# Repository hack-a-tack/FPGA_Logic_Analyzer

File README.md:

# FPGA Logic Analyzer

(NOTE TO SELF: THIS MUST BE UPDATED FOR THE FINAL REVISION; REV1 IS VIRTUALLY IRRELEVANT HERE, ONLY RELEVANT IN REPORT IF USED TO DISCUSS IMPORTANT DESIGN DECISIONS)

## Project overview

(Info applies to rev. 1, update for later revisions (only final rev. matters in the README))
FPGA-based 8-channel logic analyzer implemented on iCE40UP5K. Supports 24 MHz sampling, 4096 sample depth, UART streaming and trigger logic.

Key specs:
| Spec | Value |
| ------------- | ------------- |
| FPGA | iCE40UP5K |
| Sampling channels | 8 |
| Sampling rate | 24MHz |
| Buffer | 4096 samples |
| Interface | UART |
| Programming | SPI |
| PCB | 2-layer |
| Revision | 1. |

## Architecture

// Note to self: block diagram, + explain modules briefly (less than a full sentence for each)

(insert block diagram)

(module overview:)
| Module  | Description |
| ------------- | ------------- |
| capture_engine.vhd | samples digital inputs |
| analyzer_fsm.vhd | manages logic analyzer state |
| send_engine.vhd | UART streaming of captured data |
| ... | ... |

## Photos / board render

## Performance metrics
(table of performance metrics)
| Metric  | Value |
| ------------- | ------------- |
| Sample rate | 24MHz |
| Buffer depth | 4096 samples |
| UART throughput | 3Mbaud |
| Capture latency | 3 cycles |
| LUT usage | *1420* |
| BRAM usage | *4* |

## How to build / simulate
(Brief instructions)

## Lessons and improvements

## Link to engineering report
For a more in-depth overview, check out the project report (add github route and link).

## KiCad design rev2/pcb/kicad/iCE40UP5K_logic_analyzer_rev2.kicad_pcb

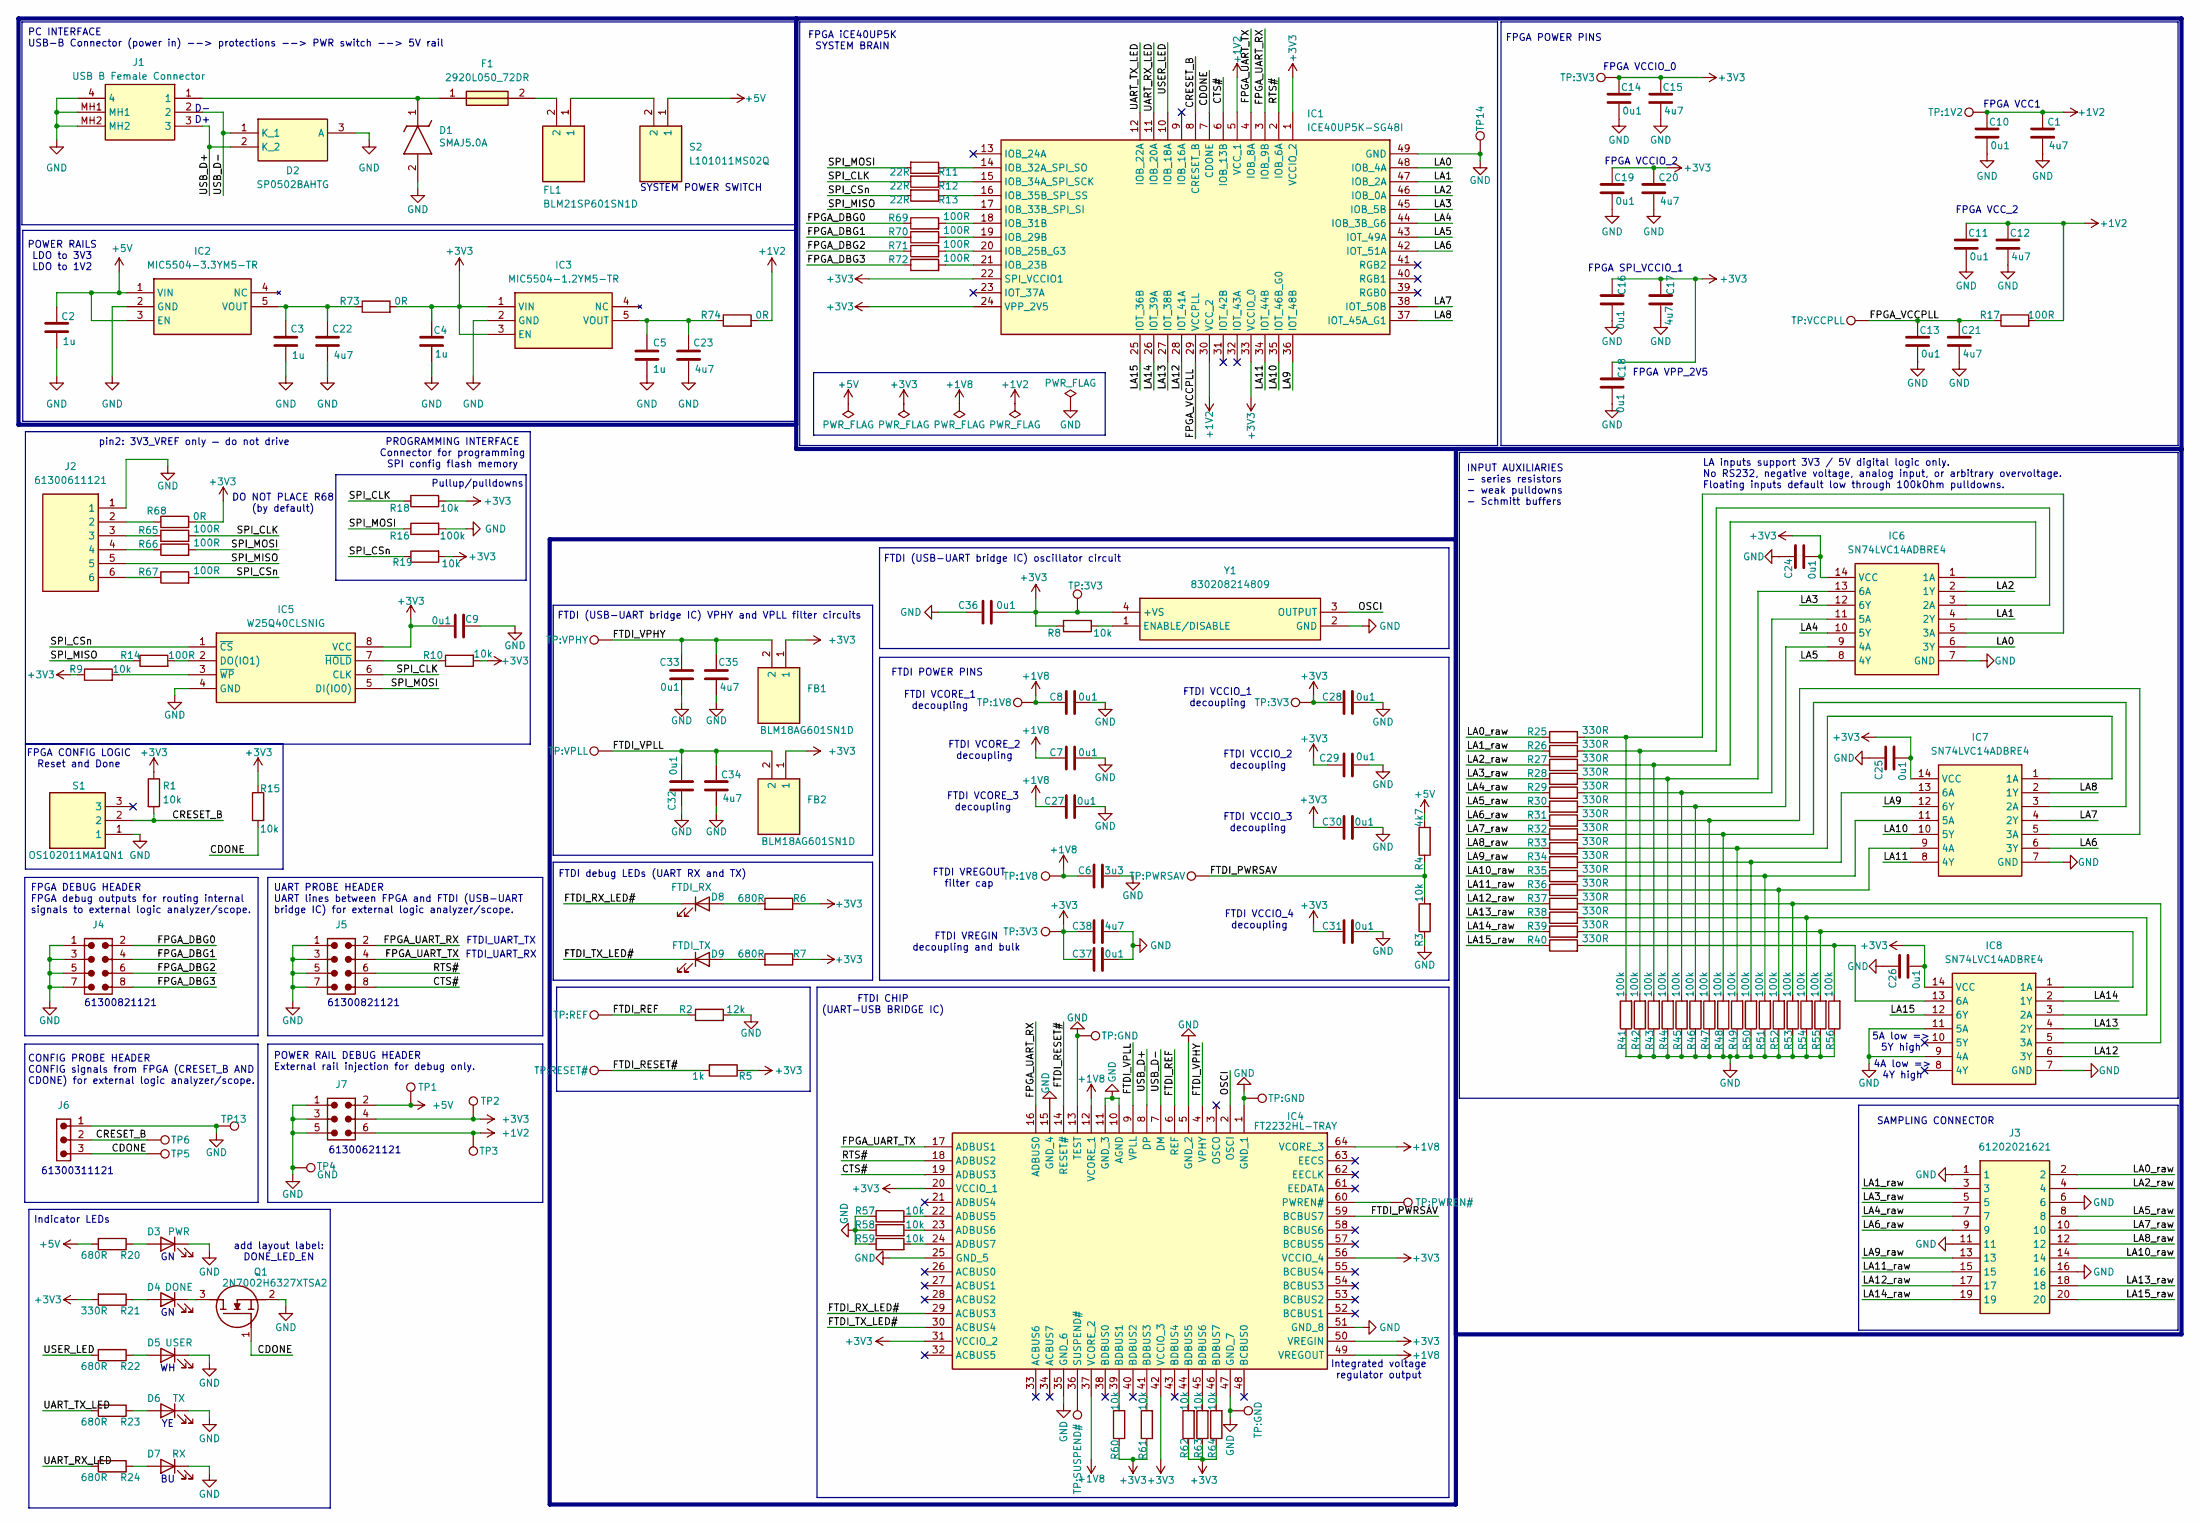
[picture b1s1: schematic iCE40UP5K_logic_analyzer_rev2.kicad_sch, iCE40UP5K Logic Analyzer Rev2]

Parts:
C1, C12, C15, C17, C20, C21, C22, C23, C34, C35, C38: 4u7; C0805
C2, C3, C4, C5: 1u; INDC1608X90N
C6: 3u3; C0805
C7, C8, C9, C10, C11, C13, C14, C16, C18, C19, C24, C25, C26, C27, C28, C29, C30, C31, C32, C33, C36, C37: 0u1; CAPC1608X95N
D1: SMAJ5.0A; DIOM5127X229N; Mouser Part Number 78-SMAJ5.0A
D2: SP0502BAHTG; SOT95P237X112-3N; Mouser Part Number 576-SP0502BAHTG
D3: PWR; 150060VS75003
D4: DONE; 150060VS75003
D5: USER; 150060WS75000
D6: TX; LEDC2012X70N
D7: RX; LEDC2012X85N
D8: FTDI_RX; LEDC2012X85N
D9: FTDI_TX; LEDC2012X70N
F1: 2920L050_72DR; FUSC7451X125N; Mouser Part Number 576-2920L050/72DR
FB1, FB2: BLM18AG601SN1D; BLM18SP221SN1B; Mouser Part Number 81-BLM11A601S
FL1: BLM21SP601SN1D; BLM21AG102BH1J; Mouser Part Number 81-BLM21SP601SN1D
IC1: ICE40UP5K-SG48I; QFN50P700X700X100-49N-D; Mouser Part Number 842-ICE40UP5K-SG48I
IC2: MIC5504-3.3YM5-TR; SOT95P280X145-5N; Mouser Part Number 998-MIC5504-3.3YM5TR
IC3: MIC5504-1.2YM5-TR; SOT95P280X145-5N; Mouser Part Number 998-MIC5504-1.2YM5TR
IC4: FT2232HL-TRAY; QFP50P1200X1200X160-64N; Mouser Part Number 895-FT2232HL-TRAY
IC5: W25Q40CLSNIG; SOIC127P600X175-8N; Mouser Part Number 454-W25Q40CLSNIG
IC6, IC7, IC8: SN74LVC14ADBRE4; SOP65P780X200-14N; Mouser Part Number 595-SN74LVC14ADBRE4
J1: USB B Female Connector; 61400416121; Mouser Part Number 710-61400416121
J2: 61300611121; HDRV6W64P0X254_1X6_1524X254X869P; Mouser Part Number 710-61300611121
J3: 61202021621; SHDR20W64P254_2X10_3306X910X885P; Mouser Part Number 710-61202021621
J4, J5: 61300821121; J_Wurth_WR-PHD_61300821121
J6: 61300311121; J_Wurth_WR-PHD_61300311121
J7: 61300621121; J_Wurth_WR-PHD_61300621121
Q1: 2N7002H6327XTSA2; SOT95P240X110-3N; Mouser Part Number 726-2N7002H6327XTSA2
R1, R3, R8, R9, R10, R15, R18, R19, R57, R58, R59, R60, R61, R62, R63, R64: 10k; R_0603_1608Metric
R2: 12k; R_0603_1608Metric
R4: 4k7; R_0603_1608Metric
R5: 1k; R_0603_1608Metric
R6, R7, R20, R22, R23, R24: 680R; R_0603_1608Metric
R11, R12, R13: 22R; R_0603_1608Metric
R14, R17, R65, R66, R67, R69, R70, R71, R72: 100R; R_0603_1608Metric
R16, R41, R42, R43, R44, R45, R46, R47, R48, R49, R50, R51, R52, R53, R54, R55, R56: 100k; R_0603_1608Metric
R21, R25, R26, R27, R28, R29, R30, R31, R32, R33, R34, R35, R36, R37, R38, R39, R40: 330R; R_0603_1608Metric
R68, R73, R74: 0R; R_0805_2012Metric
S1: OS102011MA1QN1; Mouser Part Number 611-OS102011MA1QN1
S2: L101011MS02Q; Mouser Part Number 611-L101011MS02Q
TP1: 5V; TestPoint_Pad_D1.5mm
TP2: 3V3; TestPoint_Pad_D1.5mm
TP3: 1V2; TestPoint_Pad_D1.5mm
TP4: GND; TestPoint_Pad_D1.5mm
TP5: CDONE; TestPoint_Pad_D1.0mm
TP6: CRESET_B; TestPoint_Pad_D1.0mm
TP13, TP14: GND; TestPoint_Pad_D1.0mm
TP:1V2: VCC; TestPoint_Pad_D1.0mm
TP:1V8: VREGOUT; TestPoint_Pad_D1.0mm
TP:3V3: FTDI_VCCIO; TestPoint_Pad_D1.0mm
TP:GND: GND; TestPoint_Pad_D1.0mm
TP:PWREN#: PWREN#; TestPoint_Pad_D1.0mm
TP:PWRSAV: PWRSAV#; TestPoint_Pad_D1.0mm
TP:REF: REF; TestPoint_Pad_D1.0mm
TP:RESET#: RESET#; TestPoint_Pad_D1.0mm
TP:SUSPEND#: SUSPEND#; TestPoint_Pad_D1.0mm
TP:VCCPLL: VCC_PLL; TestPoint_Pad_D1.0mm
TP:VPHY: VPHY; TestPoint_Pad_D1.0mm
TP:VPLL: VPLL; TestPoint_Pad_D1.0mm
Y1: 830208214809; Manufacturer_Part_Number 830208214809

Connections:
+1V2: C1.1, C10.1, C11.1, C12.1, IC1.5 (VCC_1), IC1.30 (VCC_2), J7.6, R17.2, R74.2, TP3.1, TP:1V2.1
+1V8: C6.1, C7.1, C8.1, C27.1, IC4.12 (VCORE_1), IC4.37 (VCORE_2), IC4.49 (VREGOUT), IC4.64 (VCORE_3), TP:1V8.1; also elsewhere on the board
+3V3: C4.1, C9.2, C14.1, C15.1, C16.1, C17.1, C18.1, C19.1, C20.1, C24.2, C25.2, C26.2, C28.1, C29.1, C30.1, C31.1, C36.2, C37.1, C38.1, FB1.1, FB2.1, IC1.1 (VCCIO_2), IC1.22 (SPI_VCCIO1), IC1.24 (VPP_2V5), IC1.33 (VCCIO_0), IC3.1 (VIN), IC3.3 (EN), IC4.20 (VCCIO_1), IC4.31 (VCCIO_2), IC4.42 (VCCIO_3), IC4.50 (VREGIN), IC4.56 (VCCIO_4), IC5.8 (VCC), IC6.14 (VCC), IC7.14 (VCC), IC8.14 (VCC), J7.4, R1.1, R5.1, R6.1, R7.1, R8.2, R9.1, R10.2, R15.1, R18.2, R19.2, R21.2, R60.1, R61.1, R62.1, R63.1, R64.1, R68.2, R73.2, TP2.1, TP:3V3.1, Y1.4 (+VS); also elsewhere on the board
+5V: C2.1, IC2.1 (VIN), IC2.3 (EN), J7.2, R4.2, R20.2, S2.1, TP1.1
/CDONE: IC1.7 (CDONE), J6.3, Q1.1 (G), R15.2, TP5.1
/CRESET_B: IC1.8 (CRESET_B), J6.2, R1.2, S1.2, TP6.1
/CTS#: IC1.6 (IOB_13B), IC4.19 (ADBUS3), J5.8
/FPGA_DBG0: J4.2, R69.1
/FPGA_DBG1: J4.4, R70.1
/FPGA_DBG2: J4.6, R71.1
/FPGA_DBG3: J4.8, R72.1
/FPGA_UART_RX: IC1.3 (IOB_9B), IC4.16 (ADBUS0), J5.2
/FPGA_UART_TX: IC1.4 (IOB_8A), IC4.17 (ADBUS1), J5.4
/FPGA_VCCPLL: C13.1, C21.1, IC1.29 (VCCPLL), R17.1, TP:VCCPLL.1
/FTDI_PWRSAV: IC4.59 (BCBUS7), R3.2, R4.1, TP:PWRSAV.1
/FTDI_REF: IC4.6 (REF), R2.1, TP:REF.1
/FTDI_RESET#: IC4.14 (RESET#), R5.2, TP:RESET#.1
/FTDI_RX_LED#: D8.1 (K), IC4.29 (ACBUS3)
/FTDI_TX_LED#: D9.1 (K), IC4.30 (ACBUS4)
/FTDI_VPHY: C33.2, C35.1, FB1.2, IC4.4 (VPHY), TP:VPHY.1
/FTDI_VPLL: C32.2, C34.1, FB2.2, IC4.9 (VPLL), TP:VPLL.1
/LA0: IC1.48 (IOB_4A), IC6.6 (3Y)
/LA0_raw: J3.2, R25.1
/LA1: IC1.47 (IOB_2A), IC6.4 (2Y)
/LA1_raw: J3.3, R26.1
/LA2: IC1.46 (IOB_0A), IC6.2 (1Y)
/LA2_raw: J3.4, R27.1
/LA3: IC1.45 (IOB_5B), IC6.12 (6Y)
/LA3_raw: J3.5, R28.1
/LA4: IC1.44 (IOB_3B_G6), IC6.10 (5Y)
/LA4_raw: J3.7, R29.1
/LA5: IC1.43 (IOT_49A), IC6.8 (4Y)
/LA5_raw: J3.8, R30.1
/LA6: IC1.42 (IOT_51A), IC7.6 (3Y)
/LA6_raw: J3.9, R31.1
/LA7: IC1.38 (IOT_50B), IC7.4 (2Y)
/LA7_raw: J3.10, R32.1
/LA8: IC1.37 (IOT_45A_G1), IC7.2 (1Y)
/LA8_raw: J3.12, R33.1
/LA9: IC1.36 (IOT_48B), IC7.12 (6Y)
/LA9_raw: J3.13, R34.1
/LA10: IC1.35 (IOT_46B_G0), IC7.10 (5Y)
/LA10_raw: J3.14, R35.1
/LA11: IC1.34 (IOT_44B), IC7.8 (4Y)
/LA11_raw: J3.15, R36.1
/LA12: IC1.28 (IOT_41A), IC8.6 (3Y)
/LA12_raw: J3.17, R37.1
/LA13: IC1.27 (IOT_38B), IC8.4 (2Y)
/LA13_raw: J3.18, R38.1
/LA14: IC1.26 (IOT_39A), IC8.2 (1Y)
/LA14_raw: J3.19, R39.1
/LA15: IC1.25 (IOT_36B), IC8.12 (6Y)
/LA15_raw: J3.20, R40.1
/OSCI: IC4.2 (OSCI), Y1.3 (OUTPUT)
/RTS#: IC1.2 (IOB_6A), IC4.18 (ADBUS2), J5.6
/SPI_CLK: IC5.6 (CLK), R12.2, R18.1, R65.2
/SPI_CSn: IC5.1 (~CS), R13.2, R19.1, R67.2
/SPI_MISO: IC1.17 (IOB_33B_SPI_SI), J2.5, R14.1
/SPI_MOSI: IC5.5 (DI(IO0)), R11.2, R16.1, R66.2
/UART_RX_LED: IC1.11 (IOB_20A), R24.2
/UART_TX_LED: IC1.12 (IOB_22A), R23.2
/USB_D+: D2.2 (K_2), IC4.8 (DP), J1.3
/USB_D-: D2.1 (K_1), IC4.7 (DM), J1.2
/USER_LED: IC1.10 (IOB_18A), R22.2
GND: C1.2, C2.2, C3.2, C4.2, C5.2, C6.2, C7.2, C8.2, C9.1, C10.2, C11.2, C12.2, C13.2, C14.2, C15.2, C16.2, C17.2, C18.2, C19.2, C20.2, C21.2, C22.2, C23.2, C24.1, C25.1, C26.1, C27.2, C28.2, C29.2, C30.2, C31.2, C32.1, C33.1, C34.2, C35.2, C36.1, C37.2, C38.2, D1.2 (A), D2.3 (A), D3.1 (K), D5.1 (K), D6.1 (K), D7.1 (K), IC1.49 (GND), IC2.2 (GND), IC3.2 (GND), IC4.1 (GND_1), IC4.5 (GND_2), IC4.10 (AGND), IC4.11 (GND_3), IC4.13 (TEST), IC4.15 (GND_4), IC4.25 (GND_5), IC4.35 (GND_6), IC4.47 (GND_7), IC4.51 (GND_8), IC5.4 (GND), IC6.7 (GND), IC7.7 (GND), IC8.7 (GND), IC8.9 (4A), IC8.11 (5A), J1.4, J1.MH1, J1.MH2, J2.1, J3.1, J3.6, J3.11, J3.16, J4.1, J4.3, J4.5, J4.7, J5.1, J5.3, J5.5, J5.7, J6.1, J7.1, J7.3, J7.5, Q1.2 (S), R2.2, R3.1, R16.2, R41.1, R42.1, R43.1, R44.1, R45.1, R46.1, R47.1, R48.1, R49.1, R50.1, R51.1, R52.1, R53.1, R54.1, R55.1, R56.1, R57.1, R58.1, R59.1, S1.1, TP4.1, TP13.1, TP14.1, TP:GND.1, Y1.2 (GND); also elsewhere on the board
unnamed: D1.1 (K), F1.1, J1.1
unnamed: D3.2 (A), R20.1
unnamed: D4.2 (A), R21.1
unnamed: D4.1 (K), Q1.3 (D)
unnamed: D5.2 (A), R22.1
unnamed: D6.2 (A), R23.1
unnamed: D7.2 (A), R24.1
unnamed: D8.2 (A), R6.2
unnamed: D9.2 (A), R7.2
unnamed: F1.2, FL1.2
unnamed: FL1.1, S2.2
unnamed: IC1.21 (IOB_23B), R72.2
unnamed: IC1.20 (IOB_25B_G3), R71.2
unnamed: IC1.19 (IOB_29B), R70.2
unnamed: IC1.18 (IOB_31B), R69.2
unnamed: IC1.14 (IOB_32A_SPI_SO), R11.1
unnamed: IC1.15 (IOB_34A_SPI_SCK), R12.1
unnamed: IC1.16 (IOB_35B_SPI_SS), R13.1
unnamed: C3.1, C22.1, IC2.5 (VOUT), R73.1
unnamed: C5.1, C23.1, IC3.5 (VOUT), R74.1
unnamed: IC4.22 (ADBUS5), R57.2
unnamed: IC4.23 (ADBUS6), R58.2
unnamed: IC4.24 (ADBUS7), R59.2
unnamed: IC4.39 (BDBUS1), R60.2
unnamed: IC4.41 (BDBUS3), R61.2
unnamed: IC4.44 (BDBUS5), R62.2
unnamed: IC4.45 (BDBUS6), R63.2
unnamed: IC4.46 (BDBUS7), R64.2
unnamed: IC4.60 (PWREN#), TP:PWREN#.1
unnamed: IC4.36 (SUSPEND#), TP:SUSPEND#.1
unnamed: IC5.2 (DO(IO1)), R14.2
unnamed: IC5.7 (~HOLD), R10.1
unnamed: IC5.3 (~WP), R9.2
unnamed: IC6.1 (1A), R27.2, R43.2
unnamed: IC6.3 (2A), R26.2, R42.2
unnamed: IC6.5 (3A), R25.2, R41.2
unnamed: IC6.9 (4A), R30.2, R46.2
unnamed: IC6.11 (5A), R29.2, R45.2
unnamed: IC6.13 (6A), R28.2, R44.2
unnamed: IC7.1 (1A), R33.2, R49.2
unnamed: IC7.3 (2A), R32.2, R48.2
unnamed: IC7.5 (3A), R31.2, R47.2
unnamed: IC7.9 (4A), R36.2, R52.2
unnamed: IC7.11 (5A), R35.2, R51.2
unnamed: IC7.13 (6A), R34.2, R50.2
unnamed: IC8.1 (1A), R39.2, R55.2
unnamed: IC8.3 (2A), R38.2, R54.2
unnamed: IC8.5 (3A), R37.2, R53.2
unnamed: IC8.13 (6A), R40.2, R56.2
unnamed: J2.2, R68.1
unnamed: J2.3, R65.1
unnamed: J2.4, R66.1
unnamed: J2.6, R67.1
unnamed: R8.1, Y1.1 (ENABLE/DISABLE)

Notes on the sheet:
FPGA VCCIO_2
FPGA VCC1
POWER RAILS LDO to 3V3 LDO to 1V2
FTDI VCORE_3 decoupling
FTDI VCCIO_1 decoupling
61300311121
5A low => 5Y high
FTDI VCCIO_2 decoupling
PROGRAMMING INTERFACE Connector for programming SPI config flash memory
FTDI_UART_RX
FTDI VCORE_1 decoupling
SAMPLING CONNECTOR
CONFIG PROBE HEADER CONFIG signals from FPGA (CRESET_B AND CDONE) for external logic analyzer/scope.
LA inputs support 3V3 / 5V digital logic only. No RS232, negative voltage, analog input, or arbitrary overvoltage. Floating inputs default low through 100kOhm pulldowns.
61300821121
add layout label: DONE_LED_EN
FPGA CONFIG LOGIC Reset and Done
UART PROBE HEADER UART lines between FPGA and FTDI (USB-UART bridge IC) for external logic analyzer/scope.
61300621121
POWER RAIL DEBUG HEADER External rail injection for debug only.
D- D+
FPGA SPI_VCCIO_1
FTDI VREGIN decoupling and bulk
FPGA POWER PINS
FTDI VCCIO_4 decoupling
FPGA DEBUG HEADER FPGA debug outputs for routing internal signals to external logic analyzer/scope.
FTDI VREGOUT filter cap
FPGA VCC_2
FTDI (USB-UART bridge IC) VPHY and VPLL filter circuits
Indicator LEDs
FTDI CHIP (UART-USB BRIDGE IC)
FTDI VCCIO_3 decoupling
FTDI (USB-UART bridge IC) oscillator circuit
FTDI debug LEDs (UART RX and TX)
Pullup/pulldowns
FPGA iCE40UP5K SYSTEM BRAIN
Integrated voltage regulator output
FTDI POWER PINS
FPGA VPP_2V5
pin2: 3V3_VREF only — do not drive

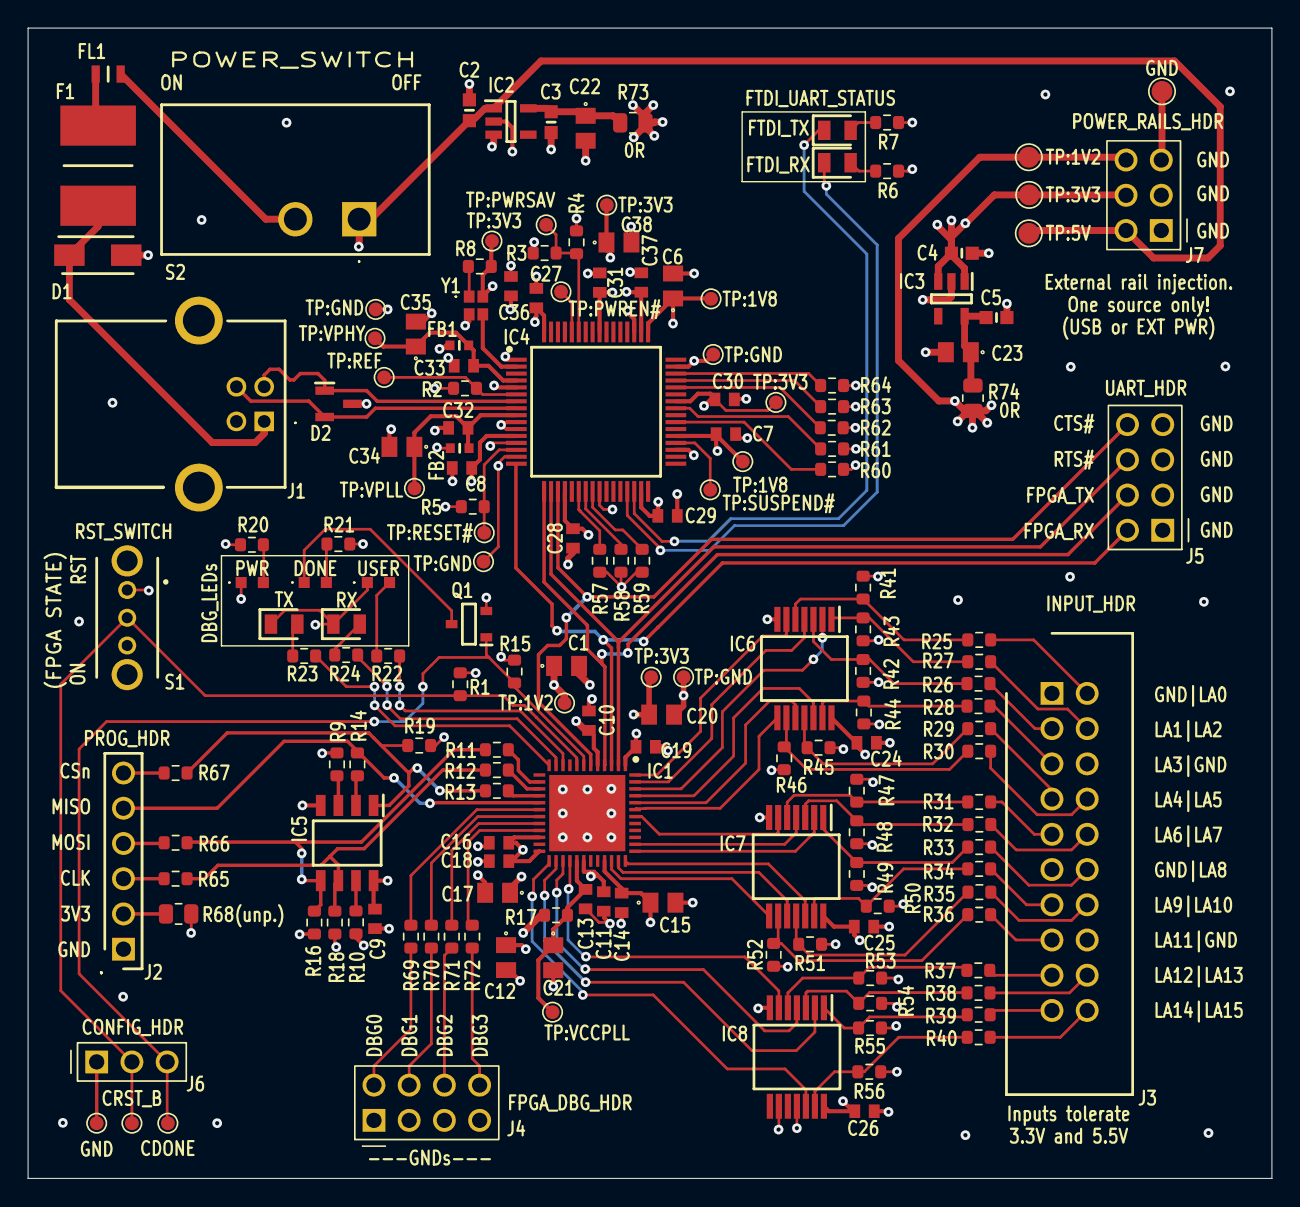
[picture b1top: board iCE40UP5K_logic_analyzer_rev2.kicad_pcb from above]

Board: 4 copper layers, 89.7 x 82.9 mm, 170 parts (0 on the bottom side), 119 nets.

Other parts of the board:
TP:1V8#2: VREGOUT; TestPoint_Pad_D1.0mm
TP:3V3#2: FTDI_VCCIO; TestPoint_Pad_D1.0mm
TP:3V3#3: VCCIO; TestPoint_Pad_D1.0mm
TP:3V3#4: VS_OSC; TestPoint_Pad_D1.0mm
TP:GND#2: GND; TestPoint_Pad_D1.0mm
TP:GND#3: TEST; TestPoint_Pad_D1.0mm

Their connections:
+1V8: TP:1V8#2.1; also elsewhere on the board
+3V3: TP:3V3#2.1, TP:3V3#3.1, TP:3V3#4.1; also elsewhere on the board
GND: TP:GND#2.1, TP:GND#3.1; also elsewhere on the board

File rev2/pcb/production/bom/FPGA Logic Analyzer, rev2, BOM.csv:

Id,Reference Designator,MPN,Qty,Description,Notes
1,IC1,ICE40UP5K-SG48I,1,"FPGA, iCE40 UP5K",
2,IC2,MIC5504-3.3YM5-TR,1,LDO (5 V to 3.3 V),
3,IC3,MIC5504-1.2YM5-TR,1,LDO (3.3 V to 1.2 V),
4,IC4,FT2232HL-REEL,1,USB-UART bridge IC,Out of stock. Buy from LCSC instead. FT2232HL-REEL
5,IC5,W25Q40CLSNIG,1,"Memory, SPI config flash, 16 Mbit","Out of stock. But can ignore since have left over from rev1. If not, replace with similar other SOIC-8"
6,"IC6, IC7, IC8",SN74LVC14ADBRE4,3,"Schmitt trigger buffer, 8 channel",
7,F1,2920L050/72DR,1,500 mA PTC polyfuse,
8,FL1,BLM21SP601SN1D,1,"2.3 A, 600 Ω ferrite bead",
9,"FB1, FB2",BLM18AG601SN1D,2,"600 Ω @ high frequency / 100 MHz class, 500 mA max DC current, 0.38 Ω max DCR, 0603",
10,Q1,2N7002H6327XTSA2,1,"NMOS, N-Ch 60V 300mA SOT-23-3, (LED driver)",
11,Y1,830208214809,1,Clock for bridge IC (Standard Clock Oscillators WE-SPXO 12.0MHz 25ppm 2.0 x 1.6mm),
12,D1,SMAJ5.0A,1,5 V unidirectional TVS diode / ESD protection,
13,D2,SP0502BAHTG,1,Data-line TVS diodes,
14,"D3, D4",150060VS75003,2,"0805 SMD LED, GN",
15,D5,150060WS75000,1,"0805 SMD LED, WH","Out of stock. But can ignore since we have one left over from rev1 (otherwise, sub with other coloured LED)"
16,"D6, D9",150080YS75000,2,"0805 SMD LED, YW",
17,"D7, D8",APT2012LVBC/D,2,"0805 SMD LED, BU",
18,"R1, R3, R8, R9, R10, R15, R18, R19, R57, R58, R59, R60, R61, R62, R63, R64",ERJ-3EKF1002V,16,"10 kΩ 0603 resistor, thick film",
19,"R11, R12, R13",RC0603JR-0722RL,3,"220 Ω 0603 resistor, thick film",
20,"R16, R41-R56",RC0603FR-07100KL,17,"100 kΩ 0603 resistor, thick film",
21,R5,RC0603FR-071KL,1,"1 kΩ, 0603",
22,"R14, R17, R65, R66, R67, R69, R70, R71, R72",560112116009,9,100 Ω 0603 resistor,
23,"R21, R25-R40",CR0603-FX-3300ELF,17,"330 Ω, 0603 SMD resistor",
24,"R6, R7, R20, R22, R23, R24",CR0603-FX-6800ELF,6,"680 Ω, 0603 SMD resistor",
25,R2,ERJ-PC3B1202V,1,"12 kΩ, 0603 SMD resistor",
26,R4,ERJ-PC3B4701V,1,"4.7 kΩ, 0603 SMD resistor",
27,"R68, R73, R74",RC0805JR-070RL,3,"0 Ohms, 0805 SMD",
28,"C7, C8, C9, C10, C11, C13, C14, C16, C18, C19, C24, C25, C26, C27, C28, C29, C30, C31, C32, C33, C36, C37",C0603C104M4RACTM,22,"100 nF / 0.1 µF 0603 capacitor (X7R, 16 V)",
29,"C2, C3, C4, C5",MBASE168SB7105KTNA18,4,"1 µF, 0603, X7R, 16 V; Low-ESR ceramic chip capacitors",
30,"C1, C12, C15, C17, C20, C21, C22, C23, C34, C35, C38",C0805C475K4RACTM,11,"4.7 µF, 0805, 16 V, X7R",
31,C6,CL10A335KP8NNNC,1,"3.3 µF, 0603, +/-10% 10V X5R",
32,S1,OS102011MA1QN1,1,Slide Switches SPDT On-On | CRESET_B,
33,S2,L101011MS02Q,1,"Slide Switch (SPST, ON/OFF) | power switch",
34,J1,61400416121,1,USB Type-B female header,
35,J2,61300611121,1,"1x6, 0.1 in (2.54 mm pitch) header",
36,J3,61202021621,1,"2x10, 0.1 in (2.54 mm pitch) shrouded header",
37,"J4, J5",61300821121,2,"2x4, 0.1 in (2.54mm pitch) header",
38,J6,61300311121,1,"1x3, 0.1 in (2.54mm pitch) header",
39,J7,61300621121,1,"2x3, 0.1 in (2.54mm pitch) header",
40,,61202023021,2,,FOR CABLE.
41,,63902015621CAB ,1,,FOR CABLE. 63902015621CAB Out of stock. Will luse 63902615621CAB and peel of 6 wires on the far side relative to the red wire

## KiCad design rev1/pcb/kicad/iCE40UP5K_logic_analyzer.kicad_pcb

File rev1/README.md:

# Revision 1

MVP FPGA logic analyzer.

## Features
- 8 digital input channels
- 4096-sample capture depth
- nominal 24 MS/s sampling
- UART readout at 921600 baud
- store-then-send architecture

## Status
Functional hardware validated.

## Key results
See measurements/processed/performance_summary.csv.

## Known limitations
- no trigger system
- no pre-trigger buffer
- no framing/checksum
- limited capture depth
- floating inputs undefined

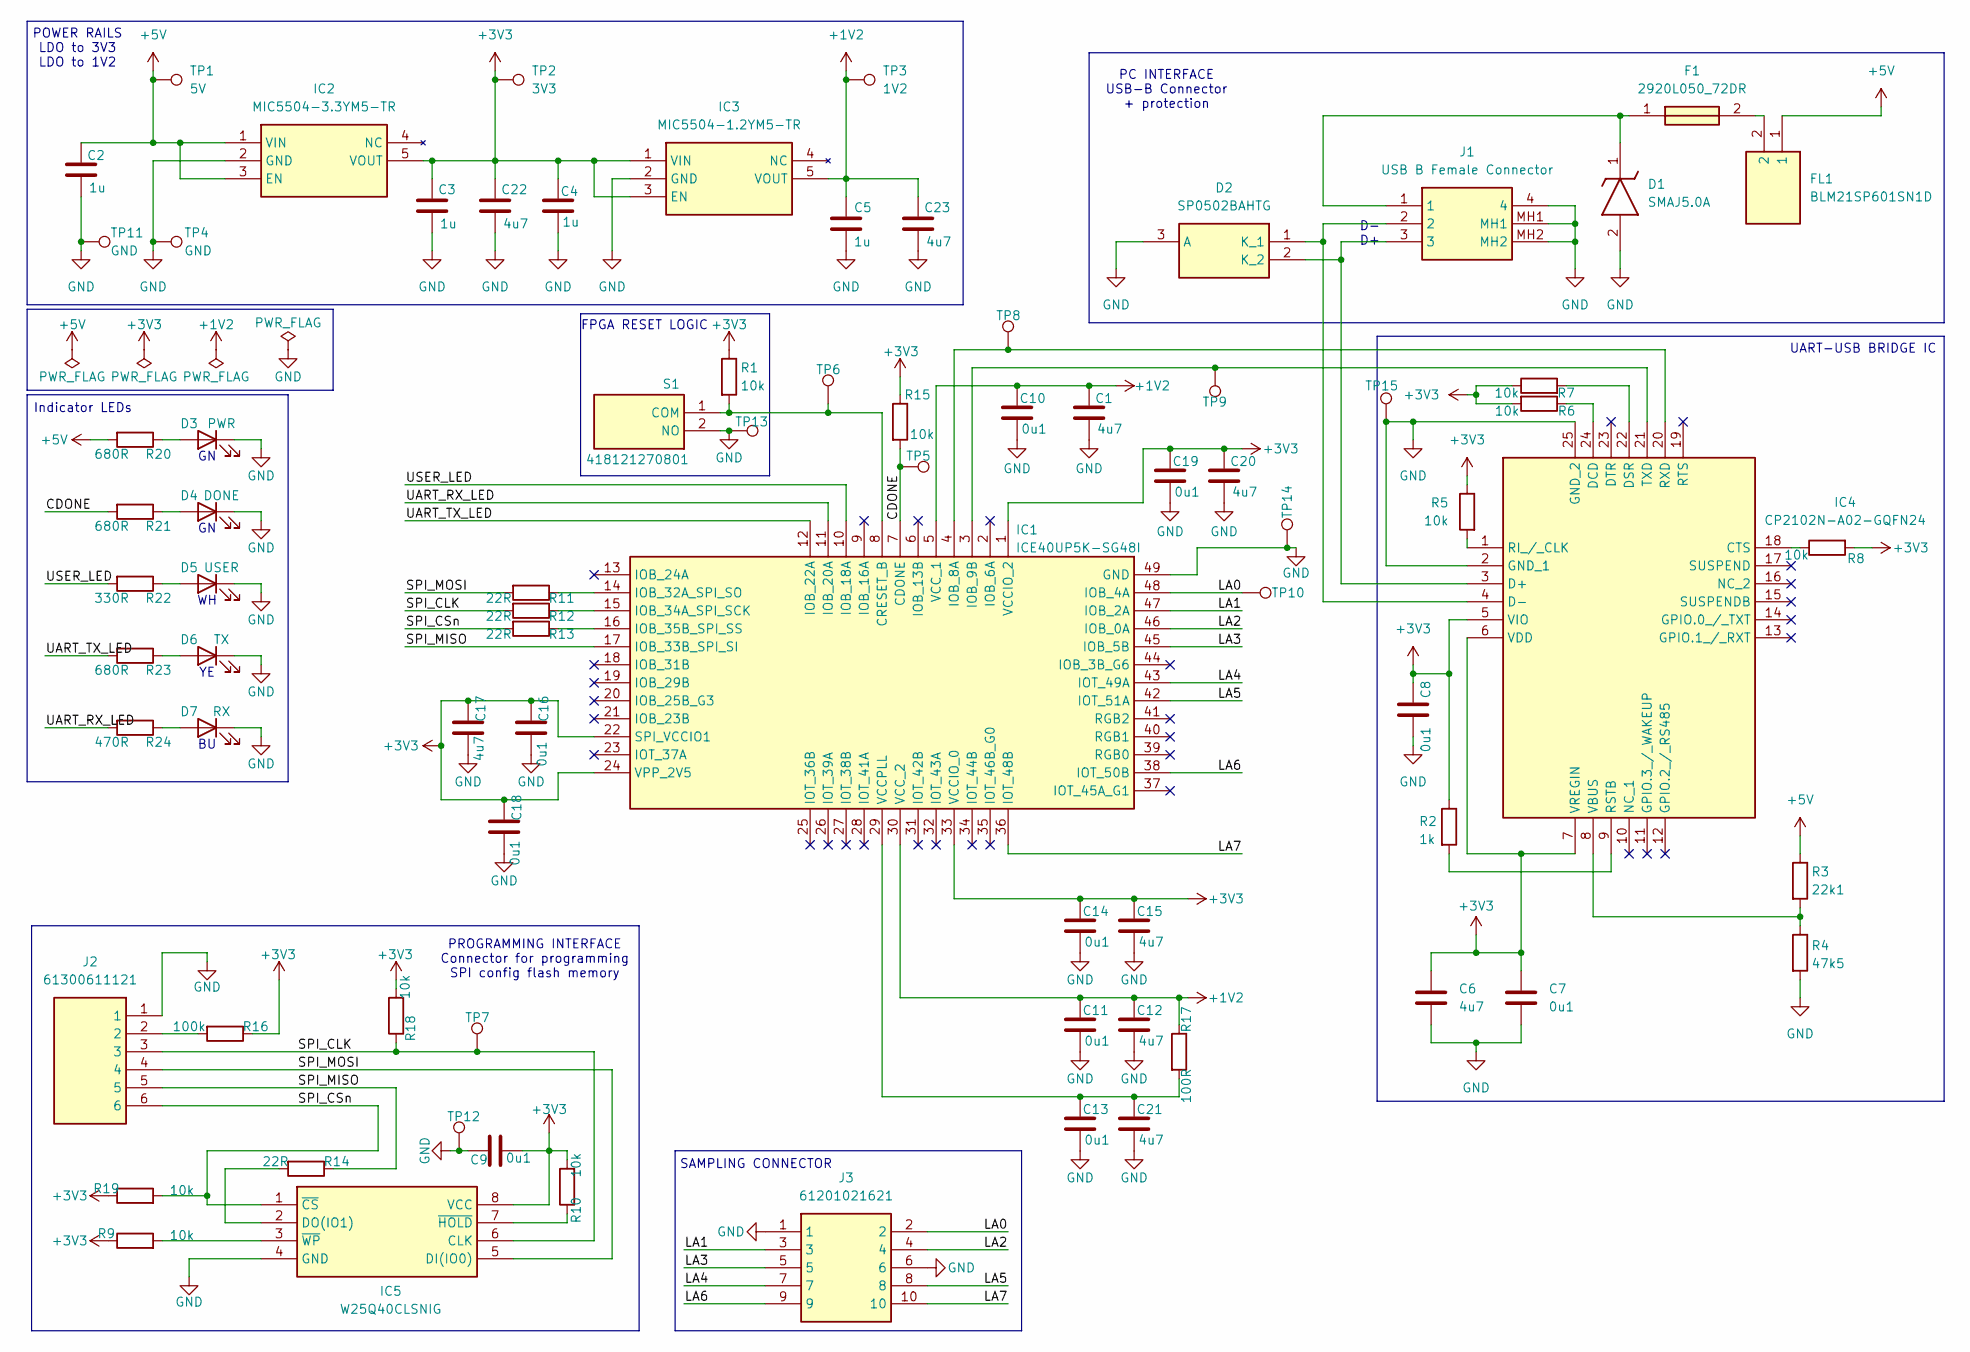
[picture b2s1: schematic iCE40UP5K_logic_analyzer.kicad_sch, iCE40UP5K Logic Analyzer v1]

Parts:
C1, C6, C12, C15, C17, C20, C21, C22, C23: 4u7; C0805
C2, C3, C4, C5: 1u; INDC1608X90N
C7, C8, C9, C10, C11, C13, C14, C16, C18, C19: 0u1; CAPC1608X95N
D1: SMAJ5.0A; DIOM5127X229N; Mouser Part Number 78-SMAJ5.0A
D2: SP0502BAHTG; SOT95P237X112-3N; Mouser Part Number 576-SP0502BAHTG
D3: PWR; 150060VS75003
D4: DONE; 150060VS75003
D5: USER; 150060WS75000
D6: TX; LEDC2012X70N
D7: RX; LEDC2012X85N
F1: 2920L050_72DR; FUSC7451X125N; Mouser Part Number 576-2920L050/72DR
FL1: BLM21SP601SN1D; BLM21AG102BH1J; Mouser Part Number 81-BLM21SP601SN1D
IC1: ICE40UP5K-SG48I; QFN50P700X700X100-49N-D; Mouser Part Number 842-ICE40UP5K-SG48I
IC2: MIC5504-3.3YM5-TR; SOT95P280X145-5N; Mouser Part Number 998-MIC5504-3.3YM5TR
IC3: MIC5504-1.2YM5-TR; SOT95P280X145-5N; Mouser Part Number 998-MIC5504-1.2YM5TR
IC4: CP2102N-A02-GQFN24; QFN50P400X400X80-25N-D; Mouser Part Number 634-CP2102NA02GQFN24
IC5: W25Q40CLSNIG; SOIC127P600X175-8N; Mouser Part Number 454-W25Q40CLSNIG
J1: USB B Female Connector; 61400416121; Mouser Part Number 710-61400416121
J2: 61300611121; HDRV6W64P0X254_1X6_1524X254X869P; Mouser Part Number 710-61300611121
J3: 61201021621; SHDR10W64P254_2X5_2036X885X925P; Mouser Part Number 710-61201021621
R1, R5, R6, R7, R8, R9, R10, R15, R18, R19: 10k; R_0603_1608Metric
R2: 1k; R_0603_1608Metric
R3: 22k1; R_0603_1608Metric
R4: 47k5; R_0603_1608Metric
R11, R12, R13, R14: 22R; R_0603_1608Metric
R16: 100k; R_0603_1608Metric
R17: 100R; R_0603_1608Metric
R20, R21, R23: 680R; R_0603_1608Metric
R22: 330R; R_0603_1608Metric
R24: 470R; R_0603_1608Metric
S1: 418121270801; Mouser Part Number N/A
TP1: 5V; TestPoint_Pad_D1.5mm
TP2: 3V3; TestPoint_Pad_D1.5mm
TP3: 1V2; TestPoint_Pad_D1.5mm
TP4, TP11: GND; TestPoint_Pad_D1.5mm
TP5: CDONE; TestPoint_Pad_D1.0mm
TP6: CRESET_B; TestPoint_Pad_D1.0mm
TP7: SPI_SCK; TestPoint_Pad_D1.0mm
TP8: FPGA_UART_TX; TestPoint_Pad_D1.0mm
TP9: FPGA_UART_RX; TestPoint_Pad_D1.0mm
TP10: CH0_sampling; TestPoint_Pad_D1.0mm
TP12, TP13, TP14, TP15: GND; TestPoint_Pad_D1.0mm

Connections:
+1V2: C1.1, C5.1, C10.1, C11.1, C12.1, C23.1, IC1.5 (VCC_1), IC1.30 (VCC_2), IC3.5 (VOUT), R17.1, TP3.1
+3V3: C3.1, C4.1, C6.1, C7.1, C8.1, C9.2, C14.1, C15.1, C16.1, C17.1, C18.1, C19.1, C20.1, C22.1, IC1.1 (VCCIO_2), IC1.22 (SPI_VCCIO1), IC1.24 (VPP_2V5), IC1.33 (VCCIO_0), IC2.5 (VOUT), IC3.1 (VIN), IC3.3 (EN), IC4.5 (VIO), IC4.6 (VDD), IC4.7 (VREGIN), IC5.8 (VCC), R1.1, R2.1, R5.1, R6.2, R7.1, R8.2, R9.1, R10.2, R15.1, R16.1, R18.2, R19.1, TP2.1
+5V: C2.1, FL1.1, IC2.1 (VIN), IC2.3 (EN), R3.1, R20.2, TP1.1
/CDONE: IC1.7 (CDONE), R15.2, R21.2, TP5.1
/LA0: IC1.48 (IOB_4A), J3.2, TP10.1
/LA1: IC1.47 (IOB_2A), J3.3
/LA2: IC1.46 (IOB_0A), J3.4
/LA3: IC1.45 (IOB_5B), J3.5
/LA4: IC1.43 (IOT_49A), J3.7
/LA5: IC1.42 (IOT_51A), J3.8
/LA6: IC1.38 (IOT_50B), J3.9
/LA7: IC1.36 (IOT_48B), J3.10
/SPI_CLK: IC5.6 (CLK), J2.3, R12.2, R18.1, TP7.1
/SPI_CSn: IC5.1 (~CS), J2.6, R13.2, R19.2
/SPI_MISO: IC1.17 (IOB_33B_SPI_SI), J2.5, R14.1
/SPI_MOSI: IC5.5 (DI(IO0)), J2.4, R11.2
/UART_RX_LED: IC1.11 (IOB_20A), R24.2
/UART_TX_LED: IC1.12 (IOB_22A), R23.2
/USER_LED: IC1.10 (IOB_18A), R22.2
GND: C1.2, C2.2, C3.2, C4.2, C5.2, C6.2, C7.2, C8.2, C9.1, C10.2, C11.2, C12.2, C13.2, C14.2, C15.2, C16.2, C17.2, C18.2, C19.2, C20.2, C21.2, C22.2, C23.2, D1.2 (A), D2.3 (A), D3.1 (K), D4.1 (K), D5.1 (K), D6.1 (K), D7.1 (K), IC1.49 (GND), IC2.2 (GND), IC3.2 (GND), IC4.2 (GND_1), IC4.25 (GND_2), IC5.4 (GND), J1.4, J1.MH1, J1.MH2, J2.1, J3.1, J3.6, R4.2, S1.2 (NO), TP4.1, TP11.1, TP12.1, TP13.1, TP14.1, TP15.1
unnamed: D1.1 (K), F1.1, J1.1
unnamed: D2.1 (K_1), IC4.4 (D-), J1.2
unnamed: D2.2 (K_2), IC4.3 (D+), J1.3
unnamed: D3.2 (A), R20.1
unnamed: D4.2 (A), R21.1
unnamed: D5.2 (A), R22.1
unnamed: D6.2 (A), R23.1
unnamed: D7.2 (A), R24.1
unnamed: F1.2, FL1.2
unnamed: IC1.8 (CRESET_B), R1.2, S1.1 (COM), TP6.1
unnamed: IC1.4 (IOB_8A), IC4.20 (RXD), TP8.1
unnamed: IC1.3 (IOB_9B), IC4.21 (TXD), TP9.1
unnamed: IC1.14 (IOB_32A_SPI_SO), R11.1
unnamed: IC1.15 (IOB_34A_SPI_SCK), R12.1
unnamed: IC1.16 (IOB_35B_SPI_SS), R13.1
unnamed: C13.1, C21.1, IC1.29 (VCCPLL), R17.2
unnamed: IC4.18 (CTS), R8.1
unnamed: IC4.24 (DCD), R6.1
unnamed: IC4.22 (DSR), R7.2
unnamed: IC4.1 (RI_/_CLK), R5.2
unnamed: IC4.9 (RSTB), R2.2
unnamed: IC4.8 (VBUS), R3.2, R4.1
unnamed: IC5.2 (DO(IO1)), R14.2
unnamed: IC5.7 (~HOLD), R10.1
unnamed: IC5.3 (~WP), R9.2
unnamed: J2.2, R16.2

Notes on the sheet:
POWER RAILS LDO to 3V3 LDO to 1V2
PROGRAMMING INTERFACE Connector for programming SPI config flash memory
SAMPLING CONNECTOR
FPGA RESET LOGIC
D- D+
Indicator LEDs
UART-USB BRIDGE IC
PC INTERFACE USB-B Connector + protection

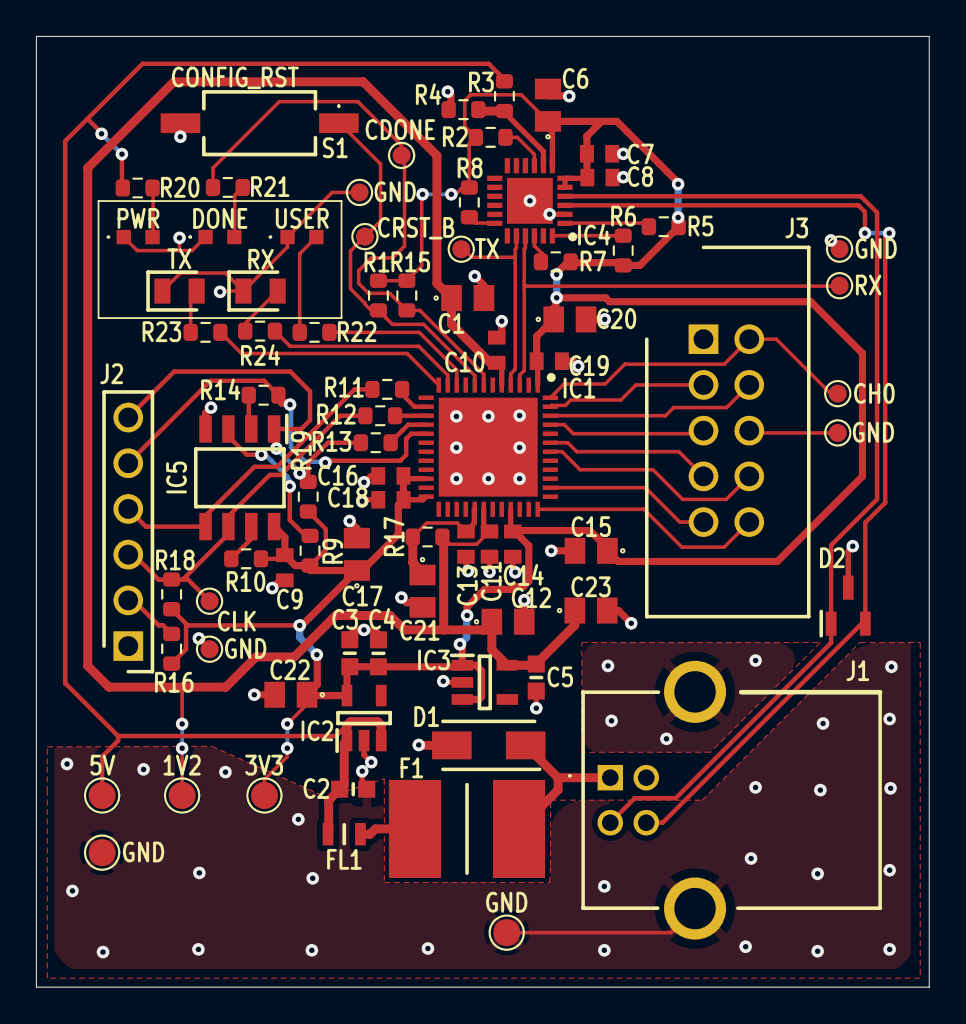
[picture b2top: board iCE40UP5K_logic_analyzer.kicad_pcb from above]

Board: 2 copper layers, 49.6 x 52.8 mm, 80 parts (0 on the bottom side), 46 nets.

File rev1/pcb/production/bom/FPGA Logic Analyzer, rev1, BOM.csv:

Item #,Description,Ref Des,MPN,Qty
1,"FPGA, iCE40 UP5K",IC1,ICE40UP5K-SG48I,1
2,1-pole DIP switch,S1,418121270801,1
3,"10 kΩ 0603 resistor, thick film","R1, R5, R6, R7, R8, R9, R10, R15, R18, R19",ERJ-3EKF1002V,10
4,"100 nF / 0.1 µF 0603 capacitor (X7R, 16 V)","C7, C8, C9, C10, C11, C13, C14, C16, C18, C19",C0603C104M4RACTM,10
5,"1x6, 0.1 in (2.54 mm pitch) header",J2,61300611121,1
6,"Memory, SPI config flash, 16 Mbit",IC5,W25Q40CLSNIG,1
7,"220 Ω 0603 resistor, thick film","R11, R12, R13, R14",RC0603JR-0722RL,4
8,"100 kΩ 0603 resistor, thick film",R16,RC0603FR-07100KL,1
9,LDO (5 V to 3.3 V),IC2,MIC5504-3.3YM5-TR,1
10,LDO (3.3 V to 1.2 V),IC3,MIC5504-1.2YM5-TR,1
11,"Low-ESR ceramic chip capacitors; 1 µF, 0603, X7R, 16 V","C2, C3, C4, C5",MBASE168SB7105KTNA18,4
12,USB Type-B female header,J1,61400416121,1
13,500 mA PTC polyfuse,F1,2920L050/72DR,1
14,"2.3 A, 600 Ω ferrite bead",FL1,BLM21SP601SN1D,1
15,5 V unidirectional TVS diode / ESD protection,D1,SMAJ5.0A,1
16,USB-UART bridge IC,IC4,CP2102N-A02-GQFN24,1
17,"1 kΩ, 0603",R2,RC0603FR-071KL,1
18,"22.1 kΩ, 0603",R3,CRCW060322K1FKEBC,1
19,"47.5 kΩ, 0603",R4,CR0603-FX-4752ELF,1
20,"4.7 µF, 0805, 16 V, X7R","C6, C1, C12, C15, C17, C20, C21, C22, C23",C0805C475K4RACTM,9
21,Data-line TVS diodes,D2,SP0502BAHTG,1
22,"2x5, 0.1 in (2.54 mm pitch) shrouded header",J3,61201021621,1
23,100 Ω 0603 resistor,R17,560112116009,1
24,"0805 SMD LED, GN","D3, D4",150060VS75003,2
25,"0805 SMD LED, WH",D5,150060WS75000,1
26,"0805 SMD LED, YW",D6,150080YS75000,1
27,"0805 SMD LED, BU",D7,APT2012LVBC/D,1
28,"330 Ω, 0603 SMD resistor",R22,CR0603-FX-3300ELF,1
29,"680 Ω, 0603 SMD resistor","R20, R21, R23",CR0603-FX-6800ELF,3
30,"470 Ω, 0603 SMD resistor",R24,RC0603FR-07470RL,1

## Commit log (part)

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2026-03-06 First commit: v1 PCB design and production files, some FPGA modules
2026-03-06 Added gitignore
2026-03-06 Testing gitignore
2026-03-06 Stop tracking current_vhdl_for_easy_review.txt
2026-03-06 Upgraded header for each VHDL module
2026-03-08 Added tx_mux architecture
2026-03-08 i_tx_busy implemented for analyzer_fsm (current modules compliant)
2026-03-08 upgraded headers
2026-03-08 Updated/upgraded analyzer_fsm TB and created tx_mux TB
2026-03-08 Added uart_tx architecture
2026-03-09 Added/finished (v1) uart_tx TB
2026-03-11 Finsihed uart_rx module
2026-03-12 Added uart_rx TB
2026-03-12 Added cmd_parser
2026-03-13 Added cmd_parser TB
2026-03-13 Added clocking module
2026-03-14 Added clocking TB, but remains to be seen if it can be simulated
2026-03-14 Added top.vhd skeleton
2026-03-14 Added trace_buffer (RAM) module
2026-03-14 Added trace_buffer (RAM) TB
2026-03-14 Added and wrote (v1) of top architecture
2026-03-15 All 9 sub- and top-level module synthesise together (without constraint files)
2026-03-22 uart_rx simulates with 0 errors
2026-03-22 uart_rx simulates with 0 errors, 0 clock drift, delta cycles implemented
2026-03-22 uart_tx simulated
2026-03-22 uart_tx (more solid) simulation
2026-03-22 cmd_parser simulated
2026-03-23 added watchdog to analyzer_fsm
2026-03-26 analyzer_fsm simulated
2026-03-29 capture_engine simulated
2026-03-29 capture_engine simulated (with no ticks = no progress TC)
2026-04-01 send_engine fully simulated
2026-04-04 trace_buffer simulated
2026-04-05 tx_mux simulated
2026-04-07 clocking simulated (with dummy entity SB_HFOSC.vhd)
2026-04-07 started top_tb
2026-04-08 top_tb simulated (TC1-3)
2026-04-09 top_TB fully sorted (TC1-5)
2026-04-10 added comment to top_tb. compiled project in iCEcube. bitmap generated
2026-04-11 added host library for python script, etc.
2026-04-11 Added VCD export functionality to la_host.py
2026-04-12 analyzer_fsm and tb updated (WD changed to improve STA); la_host.py updated; context_key.md added to docs for easier workflow
2026-04-13 added bringup.md for setup/test procedure
2026-04-13 Added self-test mode to la_host.py
2026-04-13 added rev1 images of schematic, layout, 3d render
2026-04-13 added rev1 block diagram; updated rev1 3d render
2026-04-16 added clock cycle to send_engine architecture to wait for tx_busy to go high
2026-04-18 send_engine TB sorted for updated send_engine
2026-04-18 small update to uart_tx so all bit periods are 52 clocks
2026-04-19 uart_tx sorted, full project compiled, best Fmax and WNS as of late
2026-05-04 python script ugrade; XCF file for diamond programmer
2026-05-14 Added arduino file for programming flash (basic communication, sector clear, page program and read; full bitstream TBD)
2026-05-14 bitstream_upload.ino file cleaned for testing. flash_upload.py for sending commands to program flash via arduino. arduino not ready for full programming
2026-05-14 FPGA PCB fully programmed using sorted bitstream_upload.ino file. also, bitstream added to arduino_flash_programmer folder for easier use of python script
2026-05-14 cleanup of programming files. added programming_notes.md
2026-05-14 cosmetic changes
2026-05-14 changed all rtl and tb files. rst is active low, so all 0s and 1s for rst signals flipped
2026-05-15 LA operational. analyzer_fsm, send_engine updated (TBs to be updated for proper metrics). most up-to-date bitmap is SE4 file
2026-05-16 send_engine_tb updated to test new send_engine.
2026-05-16 i_RESET reversed for top_tb since reset is active low. full project compiled again, bitmap SE5 is newest version
2026-05-17 bitmap DEBUG2 file used to find measured sample rate. top.vhd changed to facilitate this measurement
2026-05-17 current uart_tx.vhd and top.vhd used for finding transfer time metric.
2026-05-19 completed phases 7 and 8 of bringup/testing. phase 7 csv and vcd files in output folder
2026-05-20 modified cmd_parser, top and pcf to obtain latency measurements 1 and 2 in HW
2026-05-20 modified cmd_parser, top and pcf to obtain latency measurements 4 and 5 in HW
2026-05-20 modified capture_engine, top and pcf to obtain latency measurement 3 in HW
2026-05-22 REV 1 COMPLETE. stability metrics measured. LA running top_bitmap_normal1.bin
2026-05-24 rev1 admin complete. folder structure updated and finalised. moving on to rev2 folder (to be created)
2026-05-25 first rev2 commit. updated sampling connector and added series resistors, weak pulldowns and inverting Schmitt trigger buffers. VHDL of top.vhd updated accordingly
2026-05-27 USB-UART bridge IC implementation. added LC filter to VPHY and VPLL. added caps to remaining power pins.
2026-06-01 bridge-IC finished in pcb schematic
2026-06-06 Added FPGA DEBUG HEADER to schematic. top.vhd and pcf files also updated.
2026-06-06 Added UART PROBE HEADER to schematic.
2026-06-06 Added CONFIG PROBE HEADER to schematic.
2026-06-06 Added POWER RAIL DEBUG HEADER and 0R links to LDO outputs in schematic.
2026-06-10 reworked schematic test pads. Cleaned up multiple of the schematic blocks.
2026-06-15 CRESET_B slide switch implemented in schematic.
2026-06-19 rev2 schematic fully sorted with cleanup and different sections
2026-06-22 SCHEMATIC passed design rule check (DRC).
2026-06-23 LAYOUT all components placed relatively well. Time for wiring
2026-06-24 LAYOUT in the works. SPI lines connected last
2026-06-24 LAYOUT. update to SPI lines.
2026-06-25 LAYOUT. LA inputs sorted. Note that LA12-15 have new FPGA pins (updated in notes table and PCF).
2026-06-25 LAYOUT. UART/RTS/CTS lines sorted. LEDs/DEBUGs/testpads next.
2026-06-26 LAYOUT. LEDs/DEBUG/HEADERS/testpads sorted.
